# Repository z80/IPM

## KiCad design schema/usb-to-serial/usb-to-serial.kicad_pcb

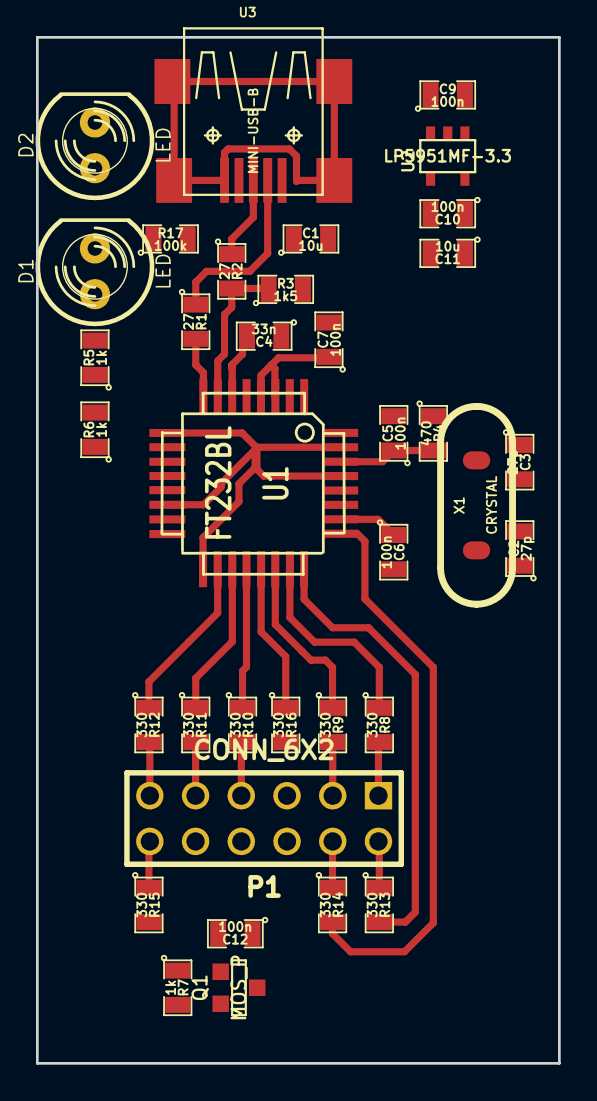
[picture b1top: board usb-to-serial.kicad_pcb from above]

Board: 2 copper layers, 29.0 x 57.0 mm, 36 parts (0 on the bottom side), 38 nets.

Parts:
C1, C11: 10u; SM0805
C2, C3: 27p; SM0805
C4: 33n; SM0805
C5, C6, C7, C9, C10, C12: 100n; SM0805
D1, D2: LED; LED-5MM
P1: CONN_6X2; pin_array_6x2
Q1: MOS_P; SOT23GDS
R1, R2: 27; SM0805
R3: 1k5; SM0805
R4: 470; SM0805
R5, R6, R7: 1k; SM0805
R8, R9, R10, R11, R12, R13, R14, R15, R16: 330; SM0805
R17: 100k; SM0805
U1: FT232BL; TQFP32
U2: LP5951MF-3.3; SOT23-5
U3: MINI-USB-B; my-mini-usb-b
X1: CRYSTAL; Quarz

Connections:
+3.3V: C10.1, C11.1, P1.10, U1.13, U2.5
/cts: R9.1, U1.22
/dcd: R11.1, U1.19
/dm: R1.2, U1.8
/dp: R2.2, R3.1, U1.7
/dsr: R10.1, U1.20
/dtr: R16.1, U1.21
/pwren: R7.2, U1.15
/ri: R12.1, U1.18
/rstout: R3.2, U1.5
/rts: R8.1, U1.23
/rxd: R13.2, U1.24
/rxled: D2.2, U1.11
/txd: R14.2, U1.25
/txden: R15.2, U1.16
/txled: D1.2, U1.12
/vccout: C12.1, P1.8, Q1.D
/xtal1: C2.1, U1.27, X1.1
/xtal2: C3.1, U1.28, X1.2
GND: C1.2, C2.2, C3.2, C4.1, C5.2, C6.2, C7.2, C9.2, C10.2, C11.2, P1.6, R17.1, U1.9, U1.14, U1.17, U1.29, U1.31, U2.2, U3.0, U3.5
unnamed: P1.12, R15.1
unnamed: P1.4, R14.1
unnamed: P1.2, R13.1
unnamed: P1.11, R12.2
unnamed: P1.9, R11.2
unnamed: P1.7, R10.2
unnamed: P1.3, R9.2
unnamed: P1.1, R8.2
unnamed: P1.5, R16.2
unnamed: R17.2, U3.4
unnamed: C12.2, Q1.G, R7.1
unnamed: C4.2, U1.6
unnamed: C5.1, R4.2, U1.30
unnamed: D2.1, R6.2
unnamed: D1.1, R5.2
unnamed: R2.1, U3.3
unnamed: R1.1, U3.2
VCC: C1.1, C6.1, C7.1, C9.1, Q1.S, R4.1, R5.1, R6.1, U1.3, U1.4, U1.26, U2.1, U2.3, U3.1

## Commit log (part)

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2012-11-16 USB doesn't work from scratch. Debugging...
2012-11-16 Ignoring additional folders.
2012-11-16 Regular USB example works. It looks I have to play starting from it adding necessary functionality.
2012-11-18 Set maximum frequency.
2012-11-18 USB is recognized.
2012-11-18 Taken chibios from repository's stable branch. But it doesn't help. i2cStart() hangs MCU up.
2012-11-18 It seems original I2C example doesn't hang up.
2012-11-18 Should be tested but i2c slave functions should be recovered.
2012-11-18 USB write works but nothing is returned back.
2012-11-19 Renamed slave functions into just one and named it i2cSlaveIoTimeout().
2012-11-19 Moved CPAL content to a separate directory.
2012-11-19 Trying to implement I2C slave mode. Most probably I need remake appropriate interrupt service routines in i2c_lld.c according to examples.
2012-11-20 Only another DB-37 suits size. Also should think for a while about rebolving motor encoder's socket.
2012-11-20 Schema edited. Have to leave just tow manipulator controls on one board. So it will be two boards for total control. Painted PCB edge with placment holes identical to previous valve_2 PCB.
2012-11-21 Placing elements.
2012-11-21 All components are within board perimeter.
2012-11-21 Schematic wasn't actually changed. It looks like just date inside of a file is different.
2012-11-22 Back imported semi routed board.
2012-11-22 Failed to route 2 wires. Just before imorting SES file.
2012-11-22 Before import SES file.
2012-11-22 Routed power for MCUs.
2012-11-22 Board with willed GND polygons.
2012-11-25 Debugging I2C.
2012-11-25 Trying to make IO with slave boards.
2012-11-25 Separated read and write queries. Bot returned value is not 0xFFFFFFFF but it is not 0 as well :(
2012-11-25 Commented out test I2C constant return.
2012-11-26 Software remote control project is imported from robocam project.
2012-11-28 xmpp
2012-11-28 Fixed send file button. Added help button.
2012-11-28 Corrected joystick ranges.
2012-11-29 Fixed help system.
2012-11-29 Turning off unused Qt modules.
2012-11-29 Learning LibreCAD.
2012-12-01 Drawing. Looks like mentioned all cable types. Made all of them at least 1m long to provide ability to connect the most distant points.
2012-12-03 Scheme for 50 in progress.
2012-12-04 Added output 220VAC wire.
2012-12-05 Finished bill of materials.
2012-12-08 Added circles but didn't cut off lines with those circles intersections.
2012-12-08 Shemes for both 50 and 1.5. And sockets different from 50 added to sockets list.
2012-12-10 Cables file is renamed.
2012-12-10 routing...
2012-12-10 so-8 package is replaced with msop-8 for ad5300 8-bit spi dac chip.
2012-12-11 Gerber files are prepared. Reference frame zero point is put close to a board corner.
2012-12-16 Designing drawings...
2012-12-18 Annotated last scheme for robot "50".
2012-12-21 Annotation is done. Or at least is seems to me it is done.
2012-12-22 Made little note for the future.
2012-12-24 Turned off output permit. It caused Power voltage to be on a normal level of 5.2V. Otherwise it is 2.7V. It sools like
2012-12-24 Test application for testing inputs.
2012-12-24 Returned output on by default.
2012-12-24 Increased I2C query period.
2012-12-24 Read should be more correct. But can't check because USB device doesn't work!
2012-12-24 When read routine is dummy USB works very well!
2012-12-26 In the case of failure I2C should be resurrected by using i2cStart() routine. And changed board file and directory!
2012-12-28 Led widget.
2012-12-28 Removed image files.
2012-12-28 Valve test window development.
2012-12-30 Removed unnecessary includes in header file.
2012-12-30 Adjusted INI files for local work.
2012-12-30 Implemented MCU control routine.
2012-12-30 Provided access to mcu variable from the outside.
2012-12-30 Made read time delays 1 microsecond. Added L293DD's out_enable turn on/off depending on values. Read, write and I2C IO only when necessary.
2012-12-31 Removed unused class.
2013-01-02 I2C stopped working.
2013-01-02 Playing with reading.
2013-01-03 Played with I2C and it's BUSY flag in slave mode. In the case of timeout with BUSY being for too long it is signaled to calling thread as returned RDY_TIMEOUT result.
2013-01-03 Compiled code.
2013-01-03 Returned the state when it worked. And it works!!!
2013-01-03 Returned back little improvement. I2C still works.
2013-01-03 Introduced separate sleep intervals for master and slave modes.
2013-01-03 Inserted condition defines.
2013-01-03 Increased I2C slave interval up to 20 milliseconds.
2013-01-03 Decreased I2C master period to 20 milliseconds. It looks like work is stable.
2013-01-03 Changed boards count. Now there are 3 boards. 1 master and 2 slaves.
2013-01-04 Watchdog works!
2013-01-04 USB on/off pin was input with internal pullup. Changed to be output pushpull.
2013-01-04 Changed boards number. Implemented report() function. But something is wrong.
2013-01-04 Found posible trouble...
2013-01-04 Fixed error associated with master board outputs.
2013-01-06 Just test firmware to make sure MCU is alive.
2013-01-13 Added moto1 and moto2 intermediate files into ignore list.
2013-01-13 LEDs initialization added.
2013-01-13 Moto2 compiles.
2013-01-15 BMSD control functions compile without errors.
2013-01-16 In this configuration LEDs work.
2013-01-16 In such configuration it hangs up.
2013-01-16 LockI/UnlockI in timer callback is bad.
2013-01-17 Router drawing.
2013-01-17 Relative encoders capture implemented. But not tested yet as well as absolute one.
2013-01-19 Fixed a few issues in bmsd_ctrl.c file.
2013-01-19 Partially written I2C IO. Starting exec_ctrl...
2013-01-19 Removed unnecessary files.
2013-01-19 Started generic I2C io.
2013-01-20 Recovered LEDs thread.
2013-01-20 Added new commands to mcuctrl. luamcuctrl is pending...
2013-01-20 Aded LEDs I2C test command. It will be the very first issue to test!
2013-01-21 Added watchdog initialization. Removed debug UART io thread.
2013-01-21 Made fixed slave address. Increased IO buffers on master side.
2013-01-21 Correct I2C slave io result.
2013-01-21 Turn hardware on step by step...
2013-01-21 Interrupt driven I2C slave. Master reports about successful write result.
2013-01-21 Still goes well. But have to off/on boards to recover IO.
2013-01-21 Command to turn LED-1 on passed!!!
2013-01-22 Turned off debug LED command invocation.
2013-01-22 UART is excluded by I2C. Whey don't work simultaneously. Only one of them.
2013-01-22 Error is caused by using one and the same DMA channels for UART2 and I2C1. It looks like should try Serial instead.
2013-01-22 Turned compile optimization on. Not sure about if it works or not but LEDs still blink...
2013-01-22 Now I see blinking! Just forgotten to insert callbacks invocation.
2013-01-22 Fixed a few obvious errors. But it looks like execPostCmd() hangs io up.
2013-01-22 USB command has reached moto_ctrl board through I2C.
2013-01-26 Designing and checking moto1 project.
2013-01-26 Made I2C address according to mainstream. E.i. 64 + 2*ind+1 for moto1 and 64+ 2*ind for moto2.
2013-01-26 Removed reference to original example.
2013-01-28 iwdgReset() without initializing IWDG caused MCU hang up.
2013-01-28 Reading I2C through USB causes reading MCU hang up. Debugging this phenomena.
2013-01-28 I2C debug in progress.
2013-01-28 In slave mode AF is not an error!!!
2013-01-28 Rebuilt moto1 and moto2. Placed IWDG reset to main loop.
2013-01-29 Added LSM303 to host.lua.
2013-01-29 Accelerometer class development...
2013-01-30 Made usb_io to wait for "<\r\n" combination.
2013-01-30 New way of transfer end recognition works. E.i. all MCU replies end with "<\r\n". And pattern search is made with boost::regex_search().
2013-01-30 Corrent data readout.
2013-01-30 Accelerometer control functions are inserted into mmcuctrl library and to luamcuctrl Lua module.
2013-02-12 Assembling and soldering procedure.
2013-02-14 Fixed errors caused by accelerometer development.
2013-02-14 Moved XMPP server to host side.
2013-02-14 Commented out debug print( "here" ) invocation. It works properly.
2013-02-14 reportInputs() function added. But isn't checked!!!
2013-02-18 valveTest() routine for testing output(s).
2013-02-22 Made dsiplay( ... ) function for sending reports about variables in text format.
2013-02-22 First byte doesn't participate to crc calculation.
2013-02-24 Switch to output is made beforehand. And some delay is provided before back switch to input.
2013-02-24 Bits mirroring routine.
2013-02-24 Checked CRC calculation. Seems it matches with Lua implementation.
2013-02-25 Added BMSD:enumCrc() routine.
2013-02-26 Commands modified. BMSD:start() and BMSD:stop() do change LED state but don't change motor. After start/stop button click motor starts. And speed/dir commands work. But can't make it work without but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
2013-02-28 Modified BMSD status cmd.
2013-03-05 ESCON Lua control module.
2013-03-09 Added move() method to ESCON class.
2013-03-15 Added Pawn. Playing around...
2013-03-15 To build proper main.amx it is necessary to use "-S1024 -XD10240" flags to "pawncc" command.
2013-03-16 Pawn test chaned. Added compile script.
2013-03-22 Looks like ROM located instructions works!
2013-03-31 FTDI support compiles somehow. But it doesn't mean it works.
2013-04-09 Documentation for LPC214x. Implemented joystick controls. FTDI should be remade for FT232BL.
2013-04-13 Changed scheme for easier routing.
2013-04-13 Zones doesn't work in the new KiCad version 2013-03-19.
2013-04-17 Changed to FT232BL.
2013-04-18 Made test firmware.
2013-04-18 Found a project with all peripherials of LPC2148.
2013-04-18 Filled UART1. Should be checked.
2013-04-18 Removed temporary files.
2013-04-19 UART1 transmit works.
2013-04-19 Involved ADC init and GPIO init. It's alive. But if ADC read finish loop is involved it never leaves this loop.
2013-04-19 Don't hang up. Strange changed j[2].value[0] to local variable and it stopped hanging up at this point.
2013-04-19 And now all ADC channels work. I changed frequency divider in ADC CR register. Now ADC frequency is 20Mhz/5 = 4MHz.
2013-04-19 Tried sending string to get it with Putty. But failed. Tried sending 0x00 to measure real baudrate. Got approximately 40000. To it is very likely that it's 38400.
2013-04-19 Implemented FTDI test for Windows.
2013-04-19 Added timeout and putting RTS low.
2013-04-20 Device could be opened but serial number request fails. Baud rate set fails. So It's impossible to work with the device.
2013-04-21 Remade using native COM port functionality.
2013-04-22 Commented out test functionality and uncommented work functionality.
2013-04-23 Remade JoyCtrl::query() to return read buffer after quering state. Now it doesn't work in Linux.
2013-04-23 Serial port for Qt library.
2013-04-24 PAcked struct to ocupy exactly as much space as necessary.
2013-04-25 Inserted joystick processing functionality for debugging.
2013-04-25 ADC value seems to be normal only for the very first ADC, For last three it is with reversed bytes order. Made all to be the same. But should check that!
2013-04-26 Fixed open() state in the case of open() failure.
2013-04-26 Joystick datasheet.
2013-05-15 Unmodified ref-frame calculation algorithm.
2013-05-15 Limitation is alpha1+alpha2=0.
2013-06-13 Modifying prices table.
2013-08-05 "Pult" power supply datasheets.
2013-10-31 Acceptance questions.
2013-11-14 Debugging an algorithm.
2013-11-14 With spin it also runs.
2013-11-16 Configured movements according to experiments.
2013-11-18 Movement step output.
2013-11-18 Initial state.
2013-11-18 Both movements without sensors work. Spinning works.
2013-11-18 Movement for 50 initial.
2013-11-21 Switched to "1.5".
2013-12-02 Have QR decoding for lowest and medium error correction values.
2013-12-03 Modified paper find procedure. Added squares example as is.
2013-12-03 Moving qr corners extraction to a separate class.
2013-12-04 Reading works but not always.
2013-12-04 More to calibration.
2013-12-11 Started manipulator processing.
2013-12-18 Motor datasheet.
2013-12-19 Just a debug line.
2014-02-27 Set IP address of the robot.
2014-02-27 Movement joystich is processed properly.
2014-05-09 Made displaying video using libvlc.
2014-05-22 End sensors are involved into algorithm.
2015-03-31 Added bigger delays.
2015-04-06 Made absolute encoder handling tunable.
